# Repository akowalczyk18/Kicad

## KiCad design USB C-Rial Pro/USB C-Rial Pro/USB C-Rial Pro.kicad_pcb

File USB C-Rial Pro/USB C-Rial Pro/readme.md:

# USB C-RIAL PRO 

##### USB to UART adapter using USB Type C Receptacle
------

Uses Cypress CY7C65213 USB to UART Converter
* TX and RX LEDs
* Extra pins broken out to program Arduino compatible boards

Hardware License: CERN OHL v 1.2

Documentation License: CC BY-SA 4.0 International

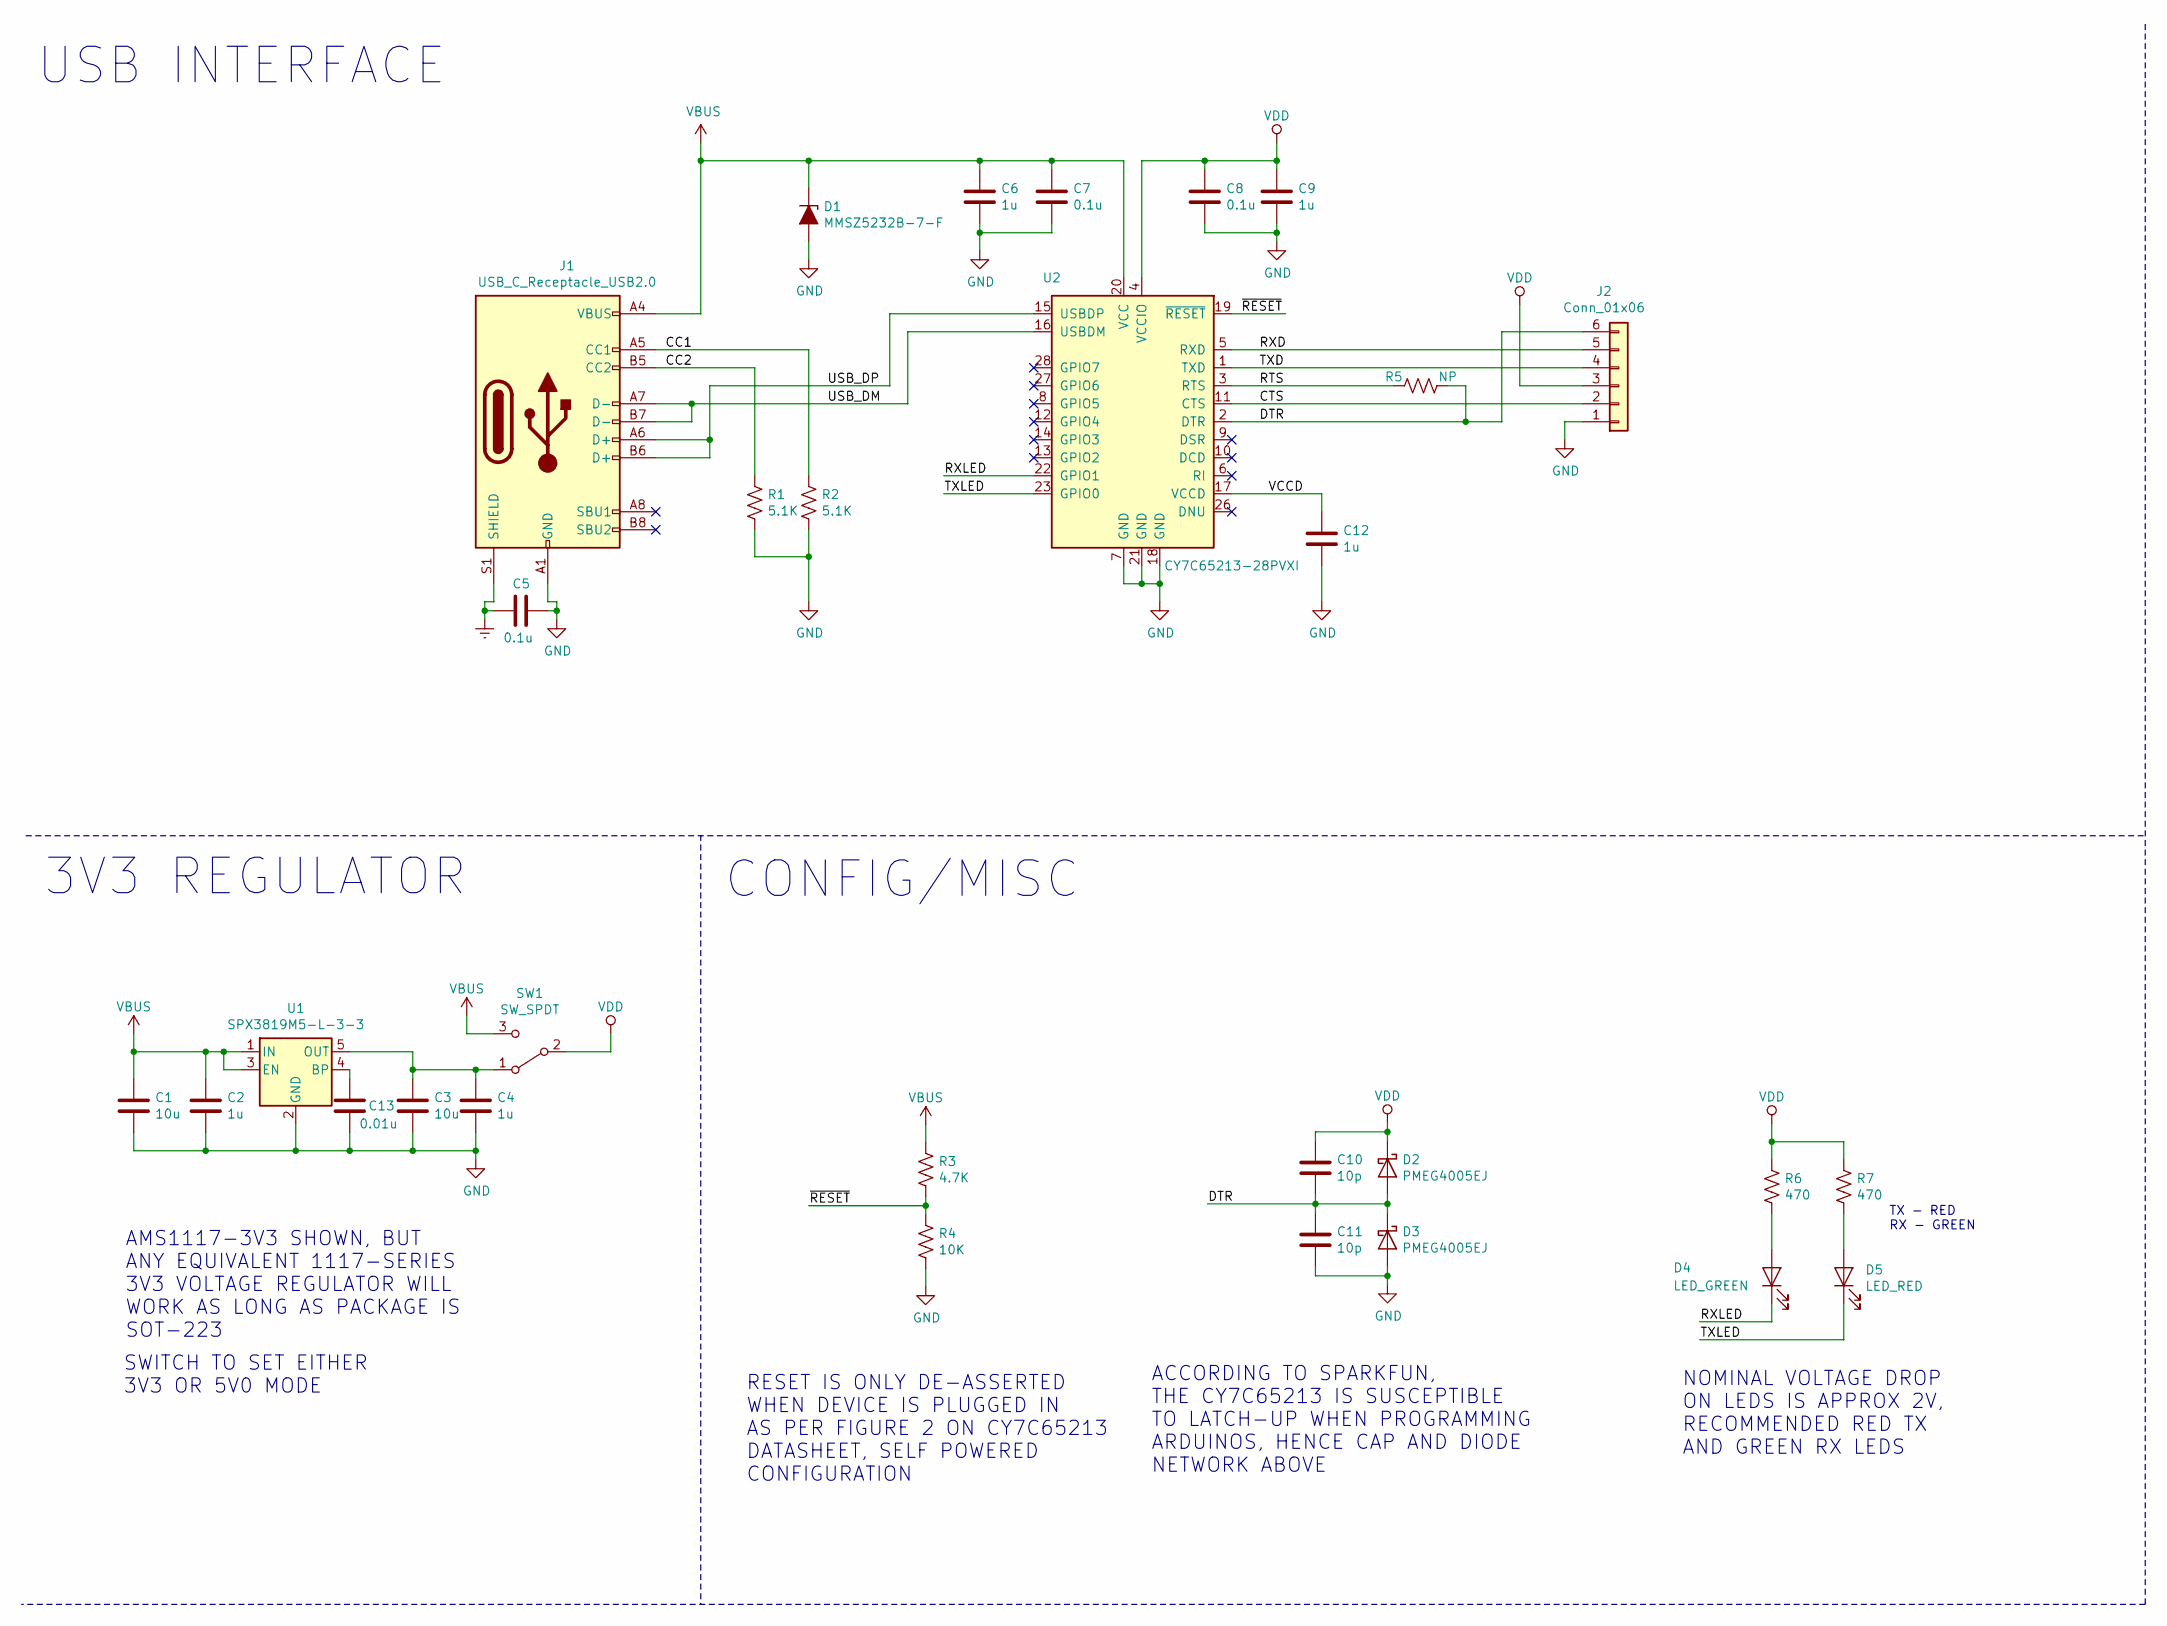
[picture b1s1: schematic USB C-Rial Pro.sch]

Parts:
C1, C3: 10u; C_0603_1608Metric
C2, C4, C6, C9, C12: 1u; C_0603_1608Metric
C5, C7, C8: 0.1u; C_0603_1608Metric
C10, C11: 10p; C_0603_1608Metric; MFG_PN C0603C100J5GACTU
C13: 0.01u; C_0603_1608Metric
D1: MMSZ5232B-7-F; D_SOD-123; MFG_PN MMSZ5232B-7-F
D2, D3: PMEG4005EJ; D_SOD-323F; MFG_PN PMEG4005EJ,115
D4: LED_GREEN; LED_0603_1608Metric
D5: LED_RED; LED_0603_1608Metric
J1: USB_C_Receptacle_USB2.0; USB_C_Receptacle_Amphenol_12401610E4-2A; MFG_PN 12401610E4#2A
J2: Conn_01x06; PinHeader_1x06_P2.54mm_Vertical; MFG_PN NO PART
R1, R2: 5.1K; R_0603_1608Metric; MFG_PN ERJ-3GEYJ512V
R3: 4.7K; R_0603_1608Metric; MFG_PN ERJ-3GEYJ472V
R4: 10K; R_0603_1608Metric; MFG_PN ERJ-3GEYJ103V
R5: NP; R_0603_1608Metric; MFG_PN NO PART
R6, R7: 470; R_0603_1608Metric; MFG_PN ERJ-3GEYJ471V
SW1: SW_SPDT; SW_SPDT_CK-JS102011SAQN; MFG_PN JS102011SAQN
U1: SPX3819M5-L-3-3; SOT-23-5
U2: CY7C65213-28PVXI; SSOP-28_5.3x10.2mm_P0.65mm; MFG_PN CY7C65213-28PVXI

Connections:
/CC1: J1.A5 (CC1), R2.1
/CC2: J1.B5 (CC2), R1.1
/CTS: J2.2, U2.11 (CTS)
/DTR: C10.2, C11.1, D2.2 (A), D3.1 (K), J2.6, R5.1, U2.2 (DTR)
/RTS: R5.2, U2.3 (RTS)
/RXD: J2.5, U2.5 (RXD)
/RXLED: D4.1 (K), U2.22 (GPIO1)
/TXD: J2.4, U2.1 (TXD)
/TXLED: D5.1 (K), U2.23 (GPIO0)
/USB_DM: J1.A7 (D-), J1.B7 (D-), U2.16 (USBDM)
/USB_DP: J1.A6 (D+), J1.B6 (D+), U2.15 (USBDP)
/VCCD: C12.1, U2.17 (VCCD)
/~RESET: R3.2, R4.1, U2.19 (~RESET)
Earth: C5.2, J1.S1 (SHIELD)
GND: C1.2, C2.2, C3.2, C4.2, C5.1, C6.2, C7.2, C8.2, C9.2, C11.2, C12.2, C13.2, D1.2 (A), D3.2 (A), J1.A1 (GND), J1.A12 (GND), J1.B1 (GND), J1.B12 (GND), J2.1, R1.2, R2.2, R4.2, U1.2 (GND), U2.7 (GND), U2.18 (GND), U2.21 (GND)
unnamed: C3.1, C4.1, SW1.1 (A), U1.5 (OUT)
unnamed: C13.1, U1.4 (BP)
unnamed: D4.2 (A), R6.2
unnamed: D5.2 (A), R7.2
VBUS: C1.1, C2.1, C6.1, C7.1, D1.1 (K), J1.A4 (VBUS), J1.A9 (VBUS), J1.B4 (VBUS), J1.B9 (VBUS), R3.1, SW1.3 (C), U1.1 (IN), U1.3 (EN), U2.20 (VCC)
VDD: C8.1, C9.1, C10.1, D2.1 (K), J2.3, R6.1, R7.1, SW1.2 (B), U2.4 (VCCIO)

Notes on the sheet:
TX - RED RX - GREEN
USB INTERFACE
3V3 REGULATOR
CONFIG/MISC
ACCORDING TO SPARKFUN, THE CY7C65213 IS SUSCEPTIBLE TO LATCH-UP WHEN PROGRAMMING ARDUINOS, HENCE CAP AND DIODE NETWORK ABOVE
RESET IS ONLY DE-ASSERTED WHEN DEVICE IS PLUGGED IN AS PER FIGURE 2 ON CY7C65213 DATASHEET, SELF POWERED CONFIGURATION
NOMINAL VOLTAGE DROP ON LEDS IS APPROX 2V, RECOMMENDED RED TX AND GREEN RX LEDS
AMS1117-3V3 SHOWN, BUT ANY EQUIVALENT 1117-SERIES 3V3 VOLTAGE REGULATOR WILL WORK AS LONG AS PACKAGE IS SOT-223
SWITCH TO SET EITHER 3V3 OR 5V0 MODE

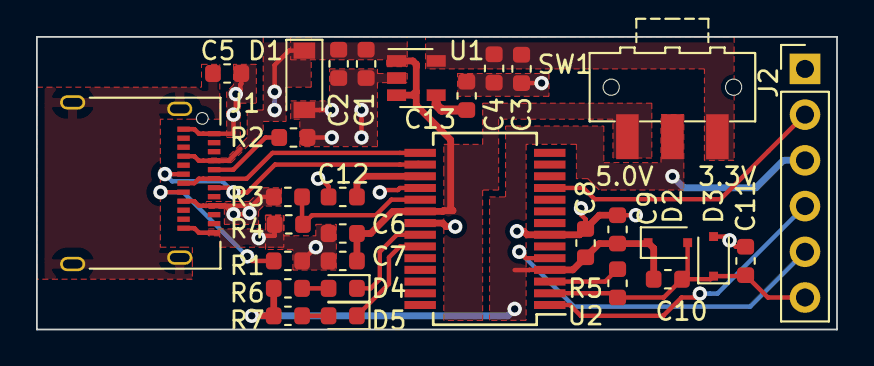
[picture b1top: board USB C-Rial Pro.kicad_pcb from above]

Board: 2 copper layers, 44.5 x 16.3 mm, 30 parts (0 on the bottom side), 21 nets.

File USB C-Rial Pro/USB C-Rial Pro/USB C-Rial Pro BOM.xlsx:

| Source: | C:\Users\agk99\Documents\GitHub\Kicad\USB C-Rial Pro\USB C-Rial Pro\USB C-Rial 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
 | Date: | 43632.923437500001
 | Tool: | Eeschema (5.1.0)-1
 | Generator: | C:\Program Files\KiCad\bin\scripting\plugins/bom_csv_custom.py
 | Component Count: | 30
 | Ref | Qnty | Value | Cmp name | Footprint | Description | MFG_PN
 | C2, C4, C12, C6, C9, | 5 | 1u | C | Capacitor_SMD:C_0603_1608Metric | Unpolarized capacitor | VJ0603G105KXJCW1BC | SUBSTITUTIONS ARE PERMITTED ON CAPACITORS, VALUE AND FOOTPRINT MUST MATCH, VOLT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
 | C3, C1, | 2 | 10u | C | Capacitor_SMD:C_0603_1608Metric | Unpolarized capacitor | GRM188R61A106ME69D
 | C7, C8, C5, | 3 | 0.1u | C | Capacitor_SMD:C_0603_1608Metric | Unpolarized capacitor | AC0603KRX7R9BB104
 | C11, C10, | 2 | 10p | C | Capacitor_SMD:C_0603_1608Metric | Unpolarized capacitor | C0603C100J5GACTU
 | C13, | 1 | 0.01u | C | Capacitor_SMD:C_0603_1608Metric | Unpolarized capacitor | GCM188R71H103KA37D
 | D1, | 1 | MMSZ5232B-7-F | D_Zener_ALT | Diode_SMD:D_SOD-123 | Zener diode, filled shape | MMSZ5232B-7-F
 | D3, D2, | 2 | PMEG4005EJ | D_Schottky | Diode_SMD:D_SOD-323F | Schottky diode | PMEG4005EJ,115
 | D4, | 1 | LED_GREEN | LED | LED_SMD:LED_0603_1608Metric | Light emitting diode | LTST-C190GKT
 | D5, | 1 | LED_RED | LED | LED_SMD:LED_0603_1608Metric | Light emitting diode | LTST-C190CKT
 | J1, | 1 | USB_C_Receptacle_USB2.0 | USB_C_Receptacle_USB2.0 | Connector_USB:USB_C_Receptacle_Amphenol_12401610E4-2A | USB 2.0-only Type-C Receptacle connector | 12401610E4#2A
 | J2, | 1 | Conn_01x06 | Conn_01x06 | Connector_PinHeader_2.54mm:PinHeader_1x06_P2.54mm_Vertical | Generic connector, single row, 01x06, script generated (kicad-library-utils/sch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 | NO PART
 | R1, R2, | 2 | 5.1K | R_US | Resistor_SMD:R_0603_1608Metric | Resistor, US symbol | ERJ-3GEYJ512V | SUBSTITUTIONS ARE PERMITTED ON RESISTORS, VALUE AND FOOTPRINT MUST MATCH, DIFFE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
 | R3, | 1 | 4.7K | R_US | Resistor_SMD:R_0603_1608Metric | Resistor, US symbol | ERJ-3GEYJ472V
 | R4, | 1 | 10K | R_US | Resistor_SMD:R_0603_1608Metric | Resistor, US symbol | ERJ-3GEYJ103V
 | R5, | 1 | NP | R_US | Resistor_SMD:R_0603_1608Metric | Resistor, US symbol | NO PART
 | R7, R6, | 2 | 470 | R_US | Resistor_SMD:R_0603_1608Metric | Resistor, US symbol | ERJ-3GEYJ471V
 | SW1, | 1 | SW_SPDT | SW_SPDT | Button_Switch_SMD:SW_SPDT_CK-JS102011SAQN | Switch, single pole double throw | JS102011SAQN
 | U1, | 1 | SPX3819M5-L-3-3 | SPX3819M5-L-3-3 | Package_TO_SOT_SMD:SOT-23-5 | 500mA Low drop-out regulator, Fixed Output 3.3V, SOT-23-5 | SPX3819M5-L-3-3 | SUBSITUTE PART: EXAR SPX3819M5-L-3-3/TR
 | U2, | 1 | CY7C65213-28PVXI | CY7C65213-28PVXI | Package_SO:SSOP-28_5.3x10.2mm_P0.65mm | USB-UART LP Bridge Controller, full speed 12Mbps, +1.71V to 5.5V VDD, UART/RS23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 | CY7C65213-28PVXI

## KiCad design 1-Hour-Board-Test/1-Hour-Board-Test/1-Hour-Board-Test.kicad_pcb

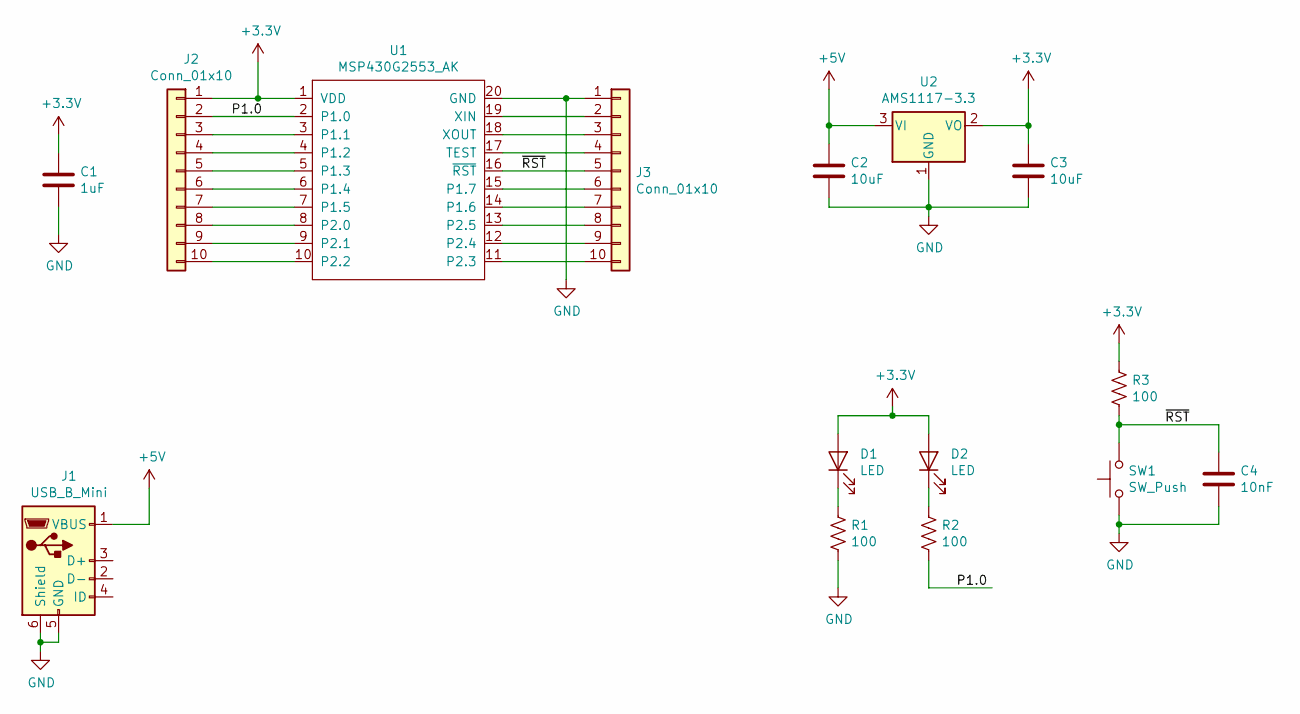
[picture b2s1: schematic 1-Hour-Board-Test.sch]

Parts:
C1: 1uF; C_0603_1608Metric_Pad1.05x0.95mm_HandSolder
C2, C3: 10uF; C_0603_1608Metric_Pad1.05x0.95mm_HandSolder
C4: 10nF; C_0603_1608Metric_Pad1.05x0.95mm_HandSolder
D1, D2: LED; LED_0603_1608Metric_Pad1.05x0.95mm_HandSolder
J1: USB_B_Mini; USB_CUI_UJ2-MBH-1-SMT-TR
J2, J3: Conn_01x10; PinHeader_1x10_P2.54mm_Vertical
R1, R2, R3: 100; R_0603_1608Metric_Pad1.05x0.95mm_HandSolder
SW1: SW_Push; B3F-1000_Modified
U1: MSP430G2553_AK; DIP-20_W7.62mm_Socket
U2: AMS1117-3.3; SOT-223-3_TabPin2

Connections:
+3V3: C1.1, C3.1, D1.2 (A), D2.2 (A), J2.1, R3.1, U1.1 (VDD), U2.2 (VO)
+5V: C2.1, J1.1 (VBUS), U2.3 (VI)
/P1.0: J2.2, R2.2, U1.2 (P1.0)
/~RST: C4.1, J3.5, R3.2, SW1.2, U1.16 (~RST)
GND: C1.2, C2.2, C3.2, C4.2, J1.5 (GND), J1.6 (Shield), J3.1, R1.2, SW1.1, U1.20 (GND), U2.1 (GND)
unnamed: D1.1 (K), R1.1
unnamed: D2.1 (K), R2.1
unnamed: J2.3, U1.3 (P1.1)
unnamed: J2.4, U1.4 (P1.2)
unnamed: J2.5, U1.5 (P1.3)
unnamed: J2.6, U1.6 (P1.4)
unnamed: J2.7, U1.7 (P1.5)
unnamed: J2.8, U1.8 (P2.0)
unnamed: J2.9, U1.9 (P2.1)
unnamed: J2.10, U1.10 (P2.2)
unnamed: J3.2, U1.19 (XIN)
unnamed: J3.3, U1.18 (XOUT)
unnamed: J3.4, U1.17 (TEST)
unnamed: J3.6, U1.15 (P1.7)
unnamed: J3.7, U1.14 (P1.6)
unnamed: J3.8, U1.13 (P2.5)
unnamed: J3.9, U1.12 (P2.4)
unnamed: J3.10, U1.11 (P2.3)

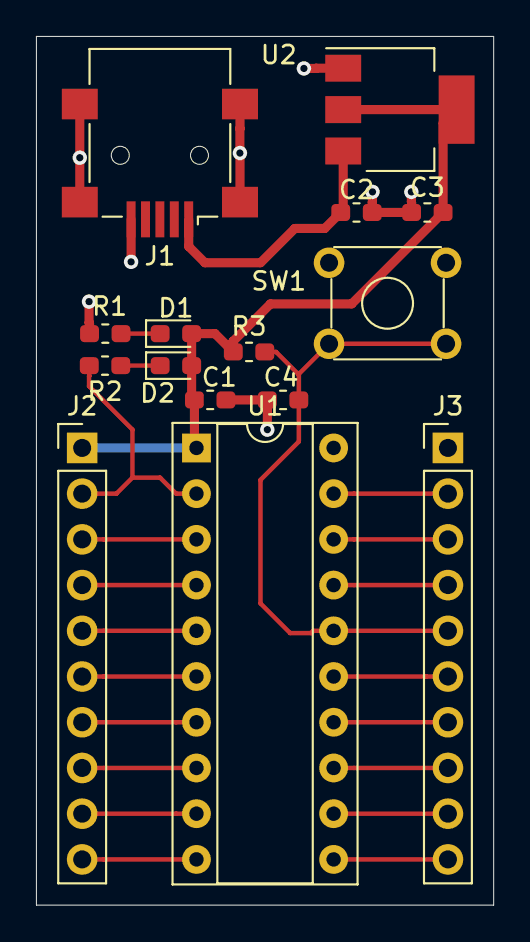
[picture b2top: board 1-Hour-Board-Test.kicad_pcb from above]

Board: 2 copper layers, 25.4 x 48.3 mm, 15 parts (0 on the bottom side), 23 nets.

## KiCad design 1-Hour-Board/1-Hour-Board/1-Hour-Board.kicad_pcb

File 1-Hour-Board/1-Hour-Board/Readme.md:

# 1-Hour-Board

##### Board designed in KiCAD for use in 1-Hour-Board KiCAD course
------

Features
* Socket for MSP430G2xxx microcontrollers
* Power LED, status LED, and reset button
* Power in from USB Mini-B connector

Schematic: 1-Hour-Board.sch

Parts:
C1: 1uF; C_0603_1608Metric_Pad1.05x0.95mm_HandSolder
C2, C3: 10uF; C_0603_1608Metric_Pad1.05x0.95mm_HandSolder
C4: 10nF; C_0603_1608Metric_Pad1.05x0.95mm_HandSolder
D1, D2: LED; LED_0603_1608Metric_Pad1.05x0.95mm_HandSolder
J1, J2: Conn_01x10; PinHeader_1x10_P2.54mm_Vertical
J3: USB_B_Mini; USB_CUI_UJ2-MBH-1-SMT-TR
R1, R2: R_US; R_0603_1608Metric_Pad1.05x0.95mm_HandSolder
R3: 47k; R_0603_1608Metric_Pad1.05x0.95mm_HandSolder
SW1: SW_Push; SW_TH_Tactile_Omron_B3F-10xx
U1: MSP430G2533IPW20; DIP-20_W7.62mm_Socket
U2: AMS1117-3.3; SOT-223-3_TabPin2

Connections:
+3V3: C1.1, C3.1, D1.2, D2.2, J1.1, R3.1, U1.1 (DVCC), U2.2 (VO)
+5V: C2.1, J3.1 (VBUS), U2.3 (VI)
/P2: J1.2, R1.2, U1.2 (TA0CLK/ACLK/CA0/A0/P1.0)
/P3: J1.3, U1.3 (TA0.0/UCA0RXD/UCA0SOMI/A1/P1.1)
/P4: J1.4, U1.4 (TA0.1/UCA0TXD/UCA0SIMO/A2/P1.2)
/P5: J1.5, U1.5 (ADC10CLK/VREF-/VeREF-/A3/P1.3)
/P6: J1.6, U1.6 (TCK/SMCLK/UCB0STE/UCA0CLK/VREF+/VeREF+/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)
/P7: J1.7, U1.7 (TMS/TA0.0/UCB0CLK/UCA0STE/A5/P1.5)
/P8: J1.8, U1.8 (P2.0/TA1.0)
/P9: J1.9, U1.9 (P2.1/TA1.1)
/P10: J1.10, U1.10 (P2.2/TA1.1)
/P11: J2.1, U1.11 (P2.3/TA1.0)
/P12: J2.2, U1.12 (P2.4/TA1.2)
/P13: J2.3, U1.13 (P2.5/TA1.2)
/P14: J2.4, U1.14 (TDI/TCLK/TA0.1/UCB0SOMI/UCB0SCL/A6/P1.6)
/P15: J2.5, U1.15 (TDO/TDI/UCB0SIMO/UCB0SDA/A7/P1.7)
/P18: J2.8, U1.18 (P2.7/XOUT)
/P19: J2.9, U1.19 (P2.6/XIN/TA0.1)
/TEST: J2.7, U1.17 (TEST/SBWTCK)
/~RST: C4.1, J2.6, R3.2, SW1.2, U1.16 (~RST~/NMI/SBWTDIO)
unnamed: D1.1, R1.1
unnamed: D2.1, R2.1

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
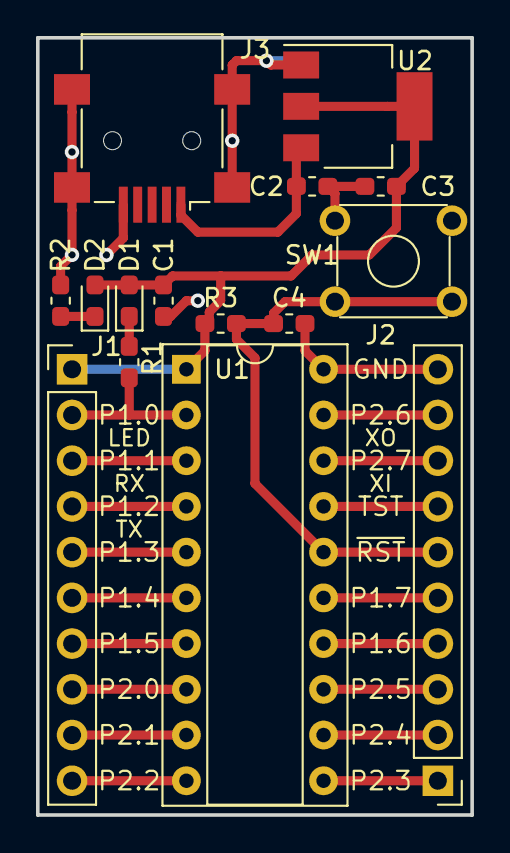
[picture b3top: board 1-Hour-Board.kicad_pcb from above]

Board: 2 copper layers, 24.1 x 43.2 mm, 15 parts (0 on the bottom side), 23 nets.

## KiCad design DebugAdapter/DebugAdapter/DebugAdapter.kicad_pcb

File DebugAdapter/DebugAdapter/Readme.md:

# Debug Adapter

##### Adapter to convert from J-Link EDU Mini to ARM 4-Pin connector (think Blue Pill)
------

Features
* 10-pin J-Link EDU Mini to 4-pin ARM, silk labeled
* Fits 2x AAA batteries to power DUT
* Switch and indicator LED for DUT power

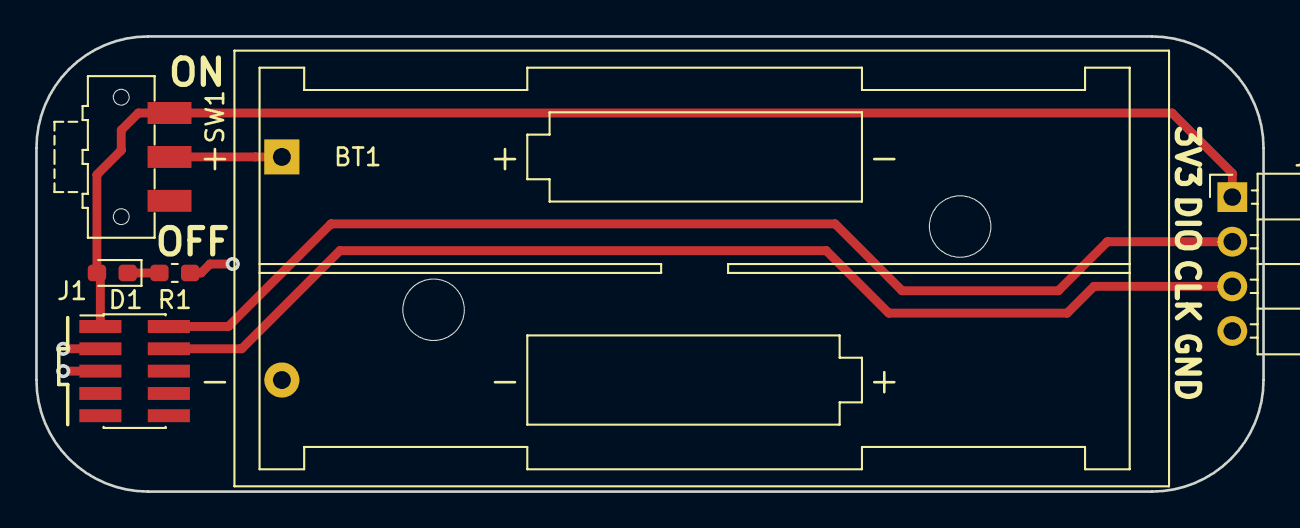
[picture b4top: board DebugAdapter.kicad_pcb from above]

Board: 2 copper layers, 69.8 x 25.9 mm, 6 parts (0 on the bottom side), 6 nets.

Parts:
BT1: Battery; BatteryHolder_Keystone_2468_2xAAA
D1: LED; D_0603_1608Metric_Pad1.05x0.95mm_HandSolder
J1: Conn_02x05_Odd_Even; PinHeader_2x05_P1.27mm_Vertical_SMD
J2: Conn_01x04; PinHeader_1x04_P2.54mm_Horizontal
R1: 1.4k; R_0603_1608Metric_Pad1.05x0.95mm_HandSolder
SW1: SW_SPDT; SW_SPDT_CK-JS102011SAQN

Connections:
+3V3: D1.2, J1.1, J2.1, SW1.1
+BATT: BT1.1, SW1.2
/SWCLK: J1.4, J2.3
/SWDIO: J1.2, J2.2
GND: BT1.2, J1.3, J1.5, J2.4, R1.2
unnamed: D1.1, R1.1

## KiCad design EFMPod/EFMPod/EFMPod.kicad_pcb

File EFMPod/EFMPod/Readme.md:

# EFM Pod Platform 

##### Open source electronics platform using EFM32 Microcontrollers
------
## EFMPod EFM32HG  
  
Uses EFM32HG322F64 Microcontroller 
* Power and data over mini USB 
* User and Power LED  
* Two user buttons and Reset button

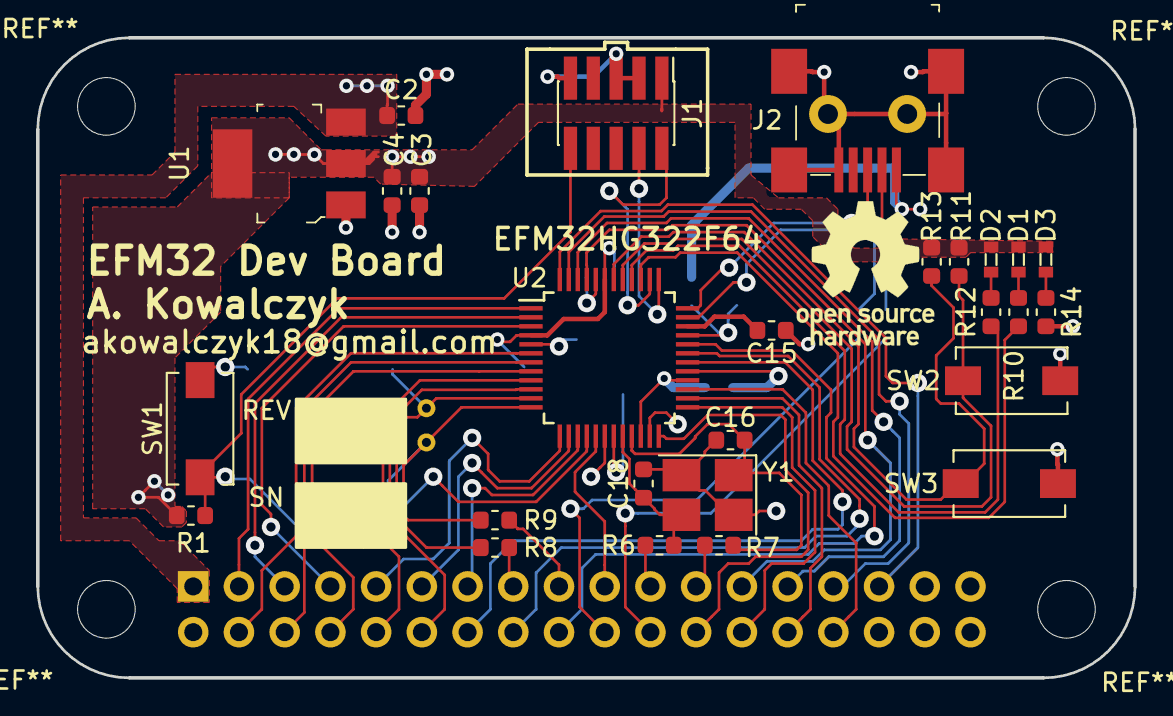
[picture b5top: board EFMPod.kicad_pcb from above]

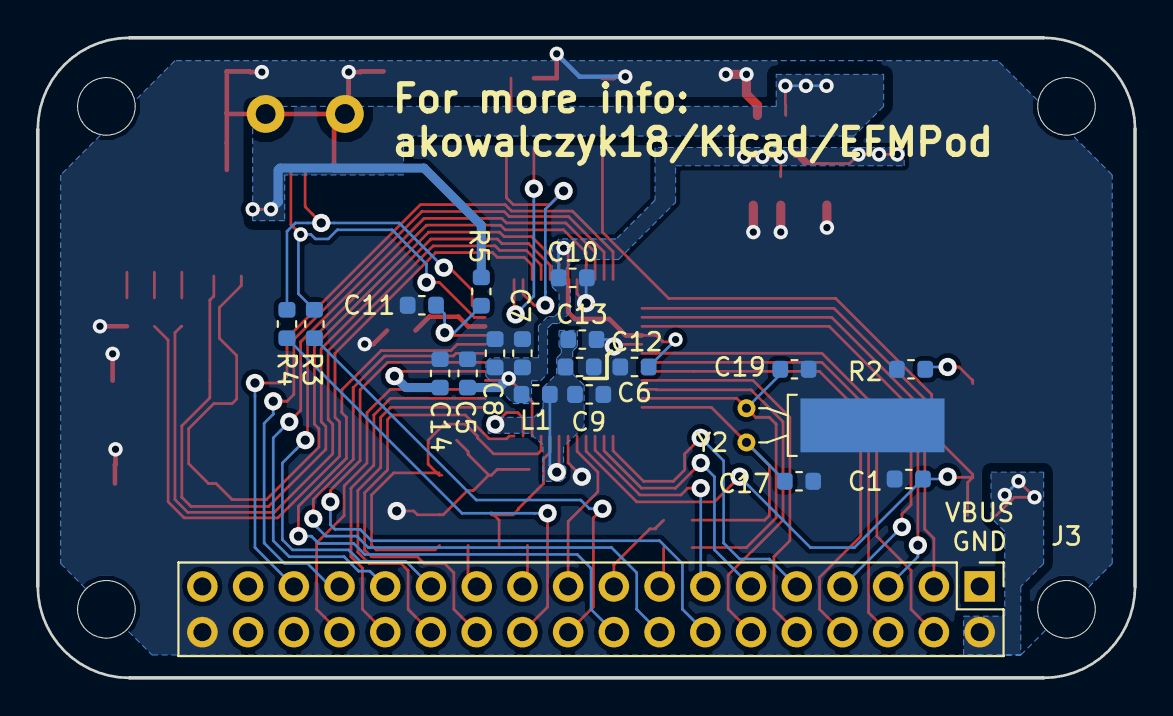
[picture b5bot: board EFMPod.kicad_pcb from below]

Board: 2 copper layers, 61.0 x 35.6 mm, 47 parts (20 on the bottom side), 53 nets.

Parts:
C1, C6, C7, C8, C10: 0.1uF; C_0603_1608Metric
C2, C3, C4, C5, C9: 10uF; C_0603_1608Metric
C11: 4.7uF; C_0603_1608Metric
C12, C13: 0.01uF; C_0603_1608Metric
C14, C15: 1uF; C_0603_1608Metric
C16, C17, C18, C19: 22pF; C_0603_1608Metric
D1, D2, D3: 2.1V; 0603
J1: Conn_02x05_Odd_Even; PinHeader_2x05_P1.27mm_Vertical_SMD
J2: UJ2-MBH-1-SMT-TR; USB_Mini_B_Female_UJ2-MBH-1-SMT-TR
J3: Conn_02x18_Odd_Even; PinHeader_2x18_P2.54mm_Vertical
L1: Ferrite_Bead; L_0603_1608Metric
R1: 100k; R_0603_1608Metric
R2, R10, R12, R14: 100; R_0603_1608Metric
R3, R4: 10; R_0603_1608Metric
R5, R6, R7, R8, R9: 0; R_0603_1608Metric
R11, R13: 47k; R_0603_1608Metric
SW1, SW2, SW3: SW_Push; SW_SPST_EVQPE1
U1: AZ1117CH-3_3TRG1; SOT-223
U2: EFM32HG322F64; TQFP-48_7x7mm_P0.5mm
Y1: Crystal_GND24; Crystal_SMD_SeikoEpson_FA238-4Pin_3.2x2.5mm_HandSoldering
Y2: Crystal_GND3; Crystal_C38-LF_D3.0mm_L8.0mm_Horizontal_1EP_style1

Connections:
+3V3: C3.1, C4.1, C5.1, C6.1, C7.1, C8.1, C10.1, D1.1, D2.1, D3.1, J1.1, J3.2, L1.2, R1.1, R11.1, R13.1, U1.2, U1.4, U2.4, U2.22, U2.28, U2.43
/DBG_SWCLK: J1.4, U2.37
/DBG_SWDIO: J1.2, U2.38
/LED0: R10.2, U2.39
/LED1: R12.2, U2.40
/PA0: J3.3, U2.1
/PA1: J3.5, U2.2
/PA2: J3.7, U2.3
/PA8: J3.9, U2.13
/PA9: J3.11, U2.14
/PA10: J3.13, U2.15
/PB7: J3.15, R8.1
/PB8: J3.17, R9.1
/PB11: J3.19, U2.17
/PB13: J3.21, R6.1
/PB14: J3.23, R7.1
/PC0: J3.4, U2.6
/PC1: J3.6, U2.7
/PC2: J3.8, U2.8
/PC3: J3.10, U2.9
/PC4: J3.12, U2.10
/PC8: J3.14, U2.30
/PC9: J3.16, U2.31
/PC10: J3.18, U2.32
/PC14: J3.20, R3.1
/PC15: J3.22, R4.1
/PD4: J3.24, U2.24
/PD5: J3.26, U2.25
/PD6: J3.28, U2.26
/PD7: J3.30, U2.27
/PE10: J3.25, U2.45
/PE11: J3.27, U2.46
/PE12: J3.29, U2.47
/PE13: J3.31, U2.48
/RTCM: C17.1, R9.2, U2.12, Y2.1
/RTCP: C19.1, R8.2, U2.11, Y2.2
/SW0: R11.2, SW2.1, U2.41
/SW1: R13.2, SW3.1, U2.42
/USB_DM: J2.2, R3.2, U2.35
/USB_DP: J2.3, R4.2, U2.36
/XTALM: C16.1, R7.2, U2.21, Y1.1
/XTALP: C18.1, R6.2, U2.20, Y1.3
/~EFM_RESET: C1.1, J1.10, R1.2, SW1.1, U2.16
GNDREF: C1.2, C2.2, C3.2, C4.2, C5.2, C6.2, C7.2, C8.2, C9.2, C10.2, C11.2, C12.2, C13.2, C14.2, C15.2, C16.2, C17.2, C18.2, C19.2, J1.3, J1.5, J1.9, J2.5, J2.SH, J3.36, R2.2, R14.2, SW2.2, SW3.2, U1.1, U2.5, U2.18, U2.44, Y1.2, Y1.4, Y2.3
unnamed: C11.1, R5.1, U2.33
unnamed: C9.1, C12.1, C13.1, L1.1, U2.19, U2.23
unnamed: C14.1, U2.29
unnamed: C15.1, U2.34
unnamed: D1.2, R10.1
unnamed: D2.2, R12.1
unnamed: D3.2, R14.1
unnamed: R2.1, SW1.2
VBUS: C2.1, J2.1, J3.1, R5.2, U1.3

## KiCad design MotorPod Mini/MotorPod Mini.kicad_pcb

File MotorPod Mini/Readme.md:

# Mini Pod Platform

##### Open source electronics platform using STM32 Microcontrollers
------
## Motor Pod Mini 
  
Add-on for STM32Pod Mini
* Can power one 12V DC motor in one direction 
* Terminal blocks for easy attachement of leads
* External interface to allow for other micros
* Serial connection to control remotely

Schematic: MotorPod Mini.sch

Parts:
D1: 1N4007; D_DO-41_SOD81_P10.16mm_Horizontal
J1: Conn_01x04; TerminalBlock_Phoenix_MKDS-1,5-4-5.08_1x04_P5.08mm_Horizont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
J2, J3: Conn_01x12; PinHeader_1x12_P2.54mm_Vertical
J4: Conn_01x05; PinHeader_1x05_P2.54mm_Vertical
Q1: TIP120; TO-220-3_Horizontal_TabUp
R1: 10k; R_Axial_DIN0207_L6.3mm_D2.5mm_P10.16mm_Horizontal
R2: 150; R_Axial_DIN0207_L6.3mm_D2.5mm_P10.16mm_Horizontal

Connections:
+3V3: J3.11, J4.1
+BATT: D1.1 (K), J1.4, J2.11
/MOTOR_N: J1.1, Q1.2
/MOTOR_P: D1.2 (A), J1.2
/MOTOR_PWM: J3.3, J4.2, R2.1
/RX: J2.9, J4.4
/TRIG: J2.7
/TX: J2.8, J4.3
Earth: J1.3, J2.12, J3.12, J4.5, Q1.3, R1.2
unnamed: Q1.1, R1.1, R2.2

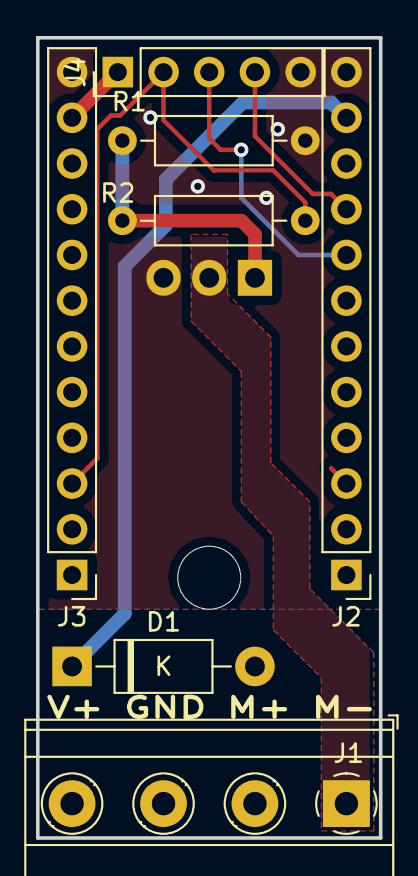
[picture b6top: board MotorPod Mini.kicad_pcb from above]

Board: 2 copper layers, 19.0 x 44.5 mm, 8 parts (1 on the bottom side), 9 nets.

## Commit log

2018-07-26 Initial Commit
    Schematic in process, layout not started
2018-07-26 Schematic done, Placement Done
    Schematic done and placement for PCB, as well as initial routing. Need to finish power planes
2018-07-27 PCB Finished
    Done with layout, 3D preview, next step is generating gerbers
2018-07-27 Preview
    Added Preview
2018-07-27 Added Readme
    added readme with picture
2018-09-01 EFM32 Schematic
    Schematic done, layout started
2018-09-01 Added stub readme
    added stub readme
2018-09-02 PCB Placement done, routing started
    Placement done, signal routing mostly done, board outline generated, mounting holes placed
2018-09-02 Placement Progress`
    Added ARM debug header, some more routing & placement, added correct switches
2018-09-07 Layout done
    Layout done, silk & gerbers next
2018-09-15 Rev 1
    Done with Rev 1, output generated
2018-09-16 STMPod & MotorPod Mini
    Prepped STMPod for manufacture,
    MotorPodMini designed in one sitting (I'm so bored...)
2018-09-16 Added readme and picture
    Readme and board preview added
2018-12-11 STM32 Mini BOM & Release
    Full release of STM32 Mini for HaD.IO
2019-01-12 SWD bug
    Made a note about the SWD bug
2019-03-05 Debug Adapter
    Debug adapter for J-Link EDU to Blue Pill/ARM 4-pin
2019-03-05 Delete file5BF1DBCD.sch
    cleaning up directory, deleted connect iv
2019-03-05 Cleaned Up
    Added Readme, render
2019-03-05 Deleted redundant files
2019-03-05 Closed KiCAD, updated files
2019-03-05 Clean up of GIT Repos
    Cleaned unneeded files from GIT
2019-03-25 1-Hour-Board-Libraries
    Added libraries for 1-Hour-Board presentation
2019-03-25 1-Hour-Board, Debug Adapter
    Added (original) 1-Hour-Board and Blue Pill Debug Adapter
2019-03-25 Add readme, render
    Added readme and rendef for 1-Hour-Board
2019-06-17 I haven't updated in a while have I...
    rip me
2019-07-14 gitignore fix
    renamed gitignore
2019-07-14 Remove excess files
    Removing unneeded files
2019-07-14 Update Repository Info
    Added Readme, render, BOM
2019-07-14 Updated readme
    fixed bullets in readme
2019-08-11 Added results picture
    Added picture of assembled board
2019-08-11 Update pic order in readme
    switched bottom and top renders
2019-11-20 EFMPod Pro start of work
    Old EFMPod board is bulky and doesn't really support bootloader functions. Making a new one that fits on breadboard and has nice USB bootloader
2019-12-11 Uploaded BOM
    BOM made available for Tindie release
2020-04-24 Added License Information
    Added the following license info to Readme:
    Hardware License: CERN OHL v 1.2
    Documentation License: CC BY-SA 4.0 International
2020-04-24 Update readme.md
    added space in readme
